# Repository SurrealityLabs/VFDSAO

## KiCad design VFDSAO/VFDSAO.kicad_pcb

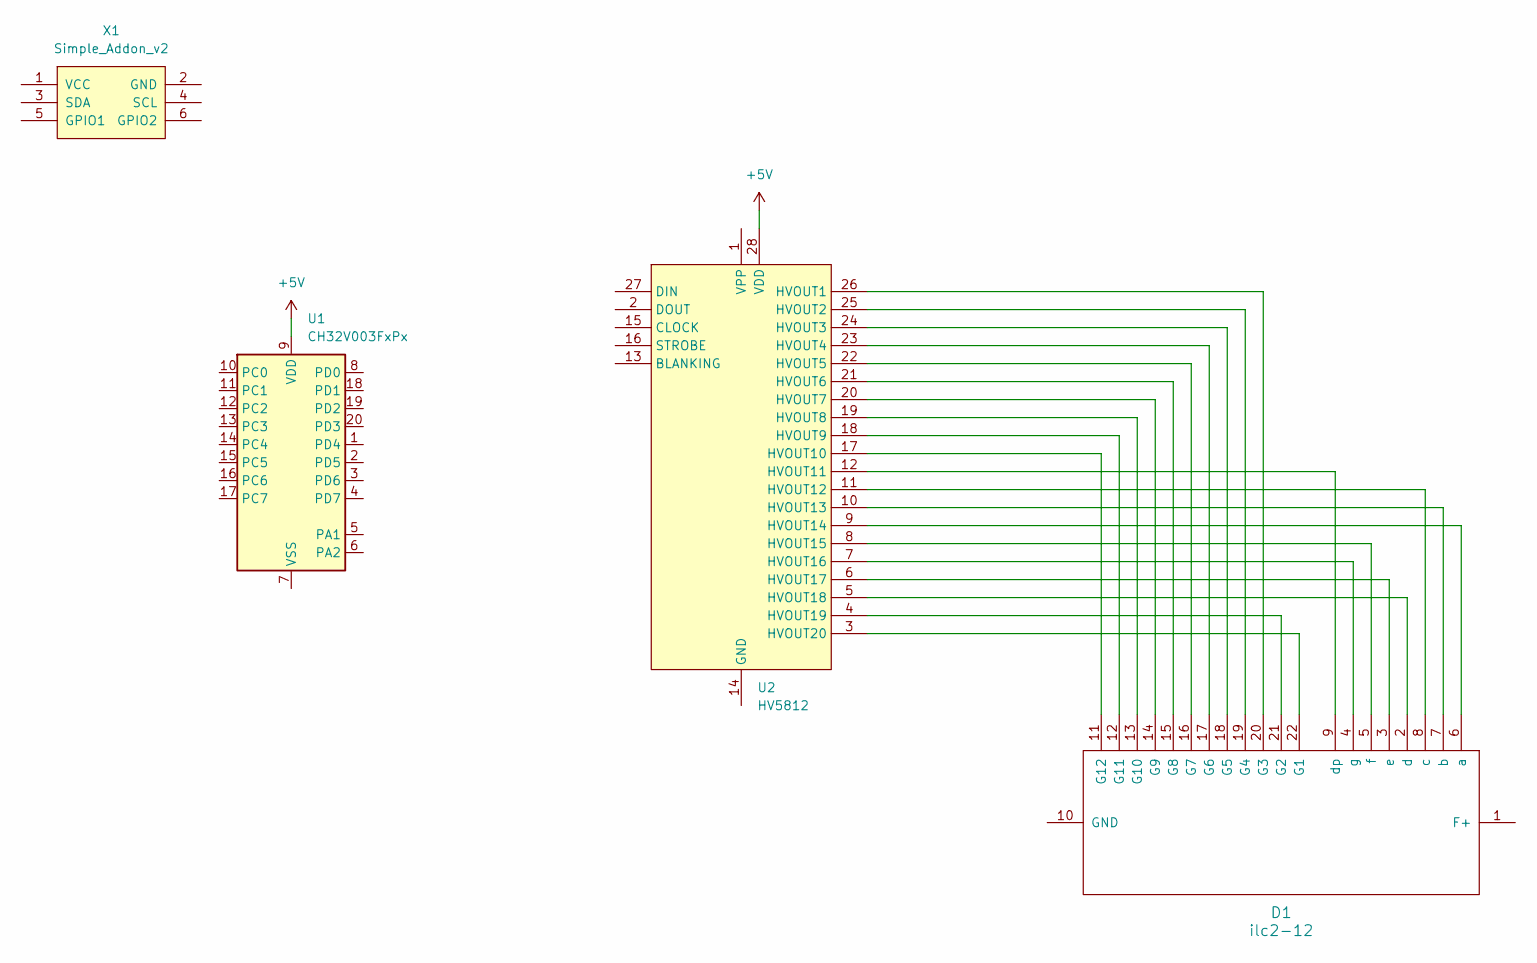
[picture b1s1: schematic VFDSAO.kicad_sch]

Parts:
D1: ilc2-12
U1: CH32V003FxPx; TSSOP-20_4.4x6.5mm_P0.65mm
U2: HV5812; SOIC-28W_7.5x17.9mm_P1.27mm
X1: Simple_Addon_v2; Simple_Addon_v2-SAO-2x3-SMD

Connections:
+5V: U1.9 (VDD), U2.28 (VDD)
unnamed: D1.22 (G1), U2.3 (HVOUT20)
unnamed: D1.21 (G2), U2.4 (HVOUT19)
unnamed: D1.20 (G3), U2.26 (HVOUT1)
unnamed: D1.19 (G4), U2.25 (HVOUT2)
unnamed: D1.18 (G5), U2.24 (HVOUT3)
unnamed: D1.17 (G6), U2.23 (HVOUT4)
unnamed: D1.16 (G7), U2.22 (HVOUT5)
unnamed: D1.15 (G8), U2.21 (HVOUT6)
unnamed: D1.14 (G9), U2.20 (HVOUT7)
unnamed: D1.13 (G10), U2.19 (HVOUT8)
unnamed: D1.12 (G11), U2.18 (HVOUT9)
unnamed: D1.11 (G12), U2.17 (HVOUT10)
unnamed: D1.6 (a), U2.9 (HVOUT14)
unnamed: D1.7 (b), U2.10 (HVOUT13)
unnamed: D1.8 (c), U2.11 (HVOUT12)
unnamed: D1.2 (d), U2.5 (HVOUT18)
unnamed: D1.9 (dp), U2.12 (HVOUT11)
unnamed: D1.3 (e), U2.6 (HVOUT17)
unnamed: D1.5 (f), U2.8 (HVOUT15)
unnamed: D1.4 (g), U2.7 (HVOUT16)

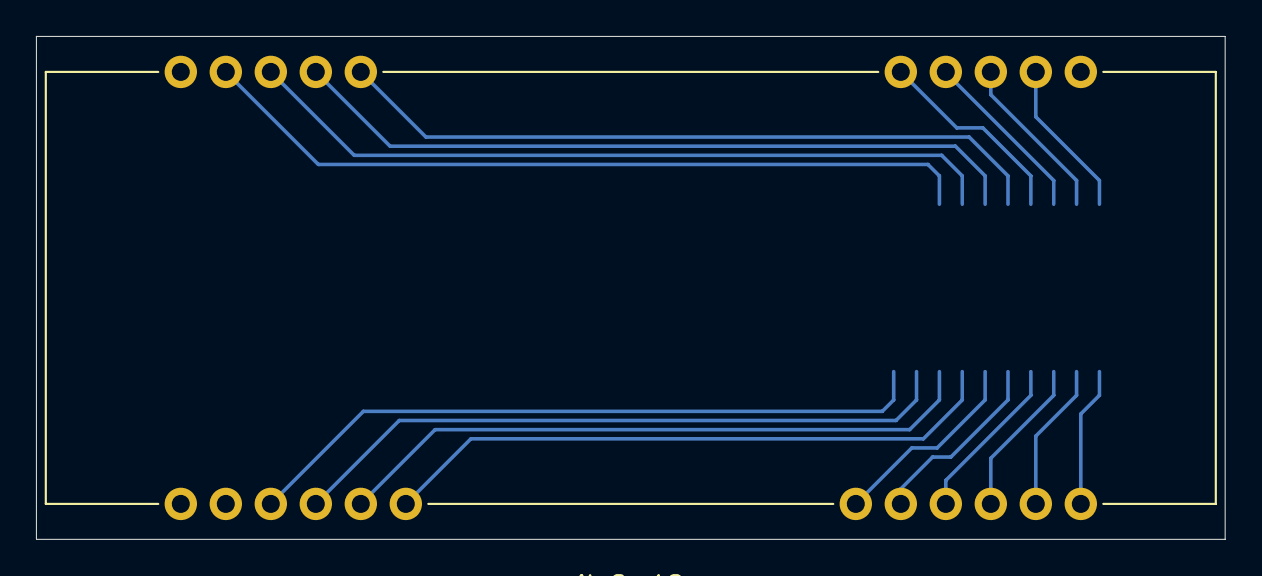
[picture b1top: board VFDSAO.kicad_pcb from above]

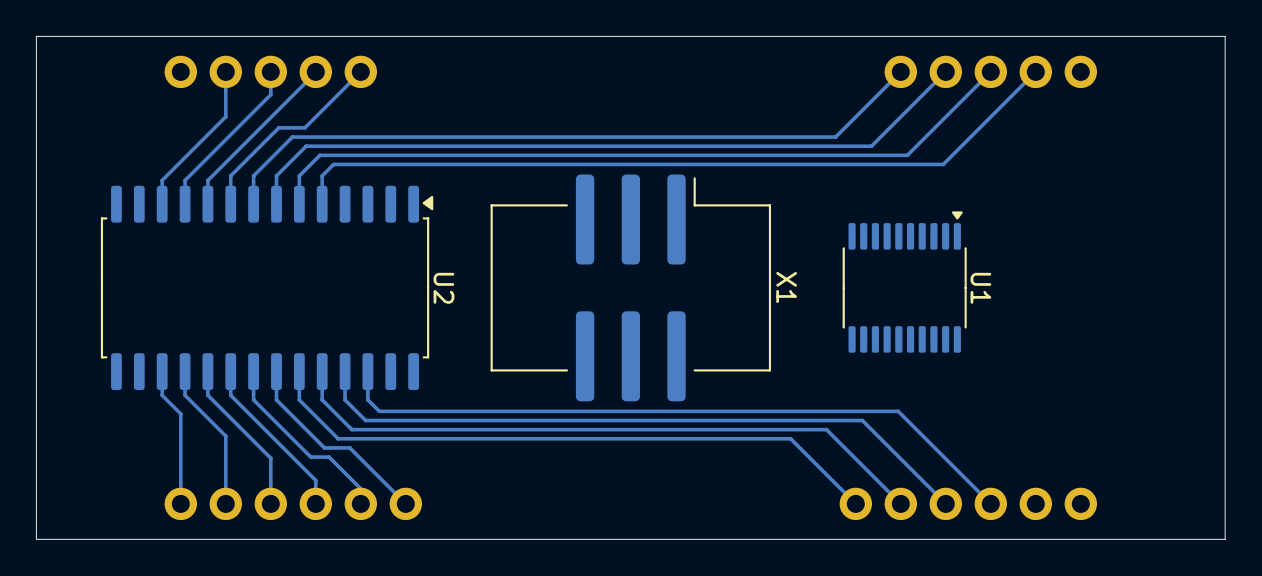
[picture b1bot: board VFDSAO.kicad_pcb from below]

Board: 2 copper layers, 66.0 x 27.9 mm, 4 parts (3 on the bottom side), 21 nets.

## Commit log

2024-12-03 Starting work on VFDSAO
2024-12-04 Adding I2C level shifters
